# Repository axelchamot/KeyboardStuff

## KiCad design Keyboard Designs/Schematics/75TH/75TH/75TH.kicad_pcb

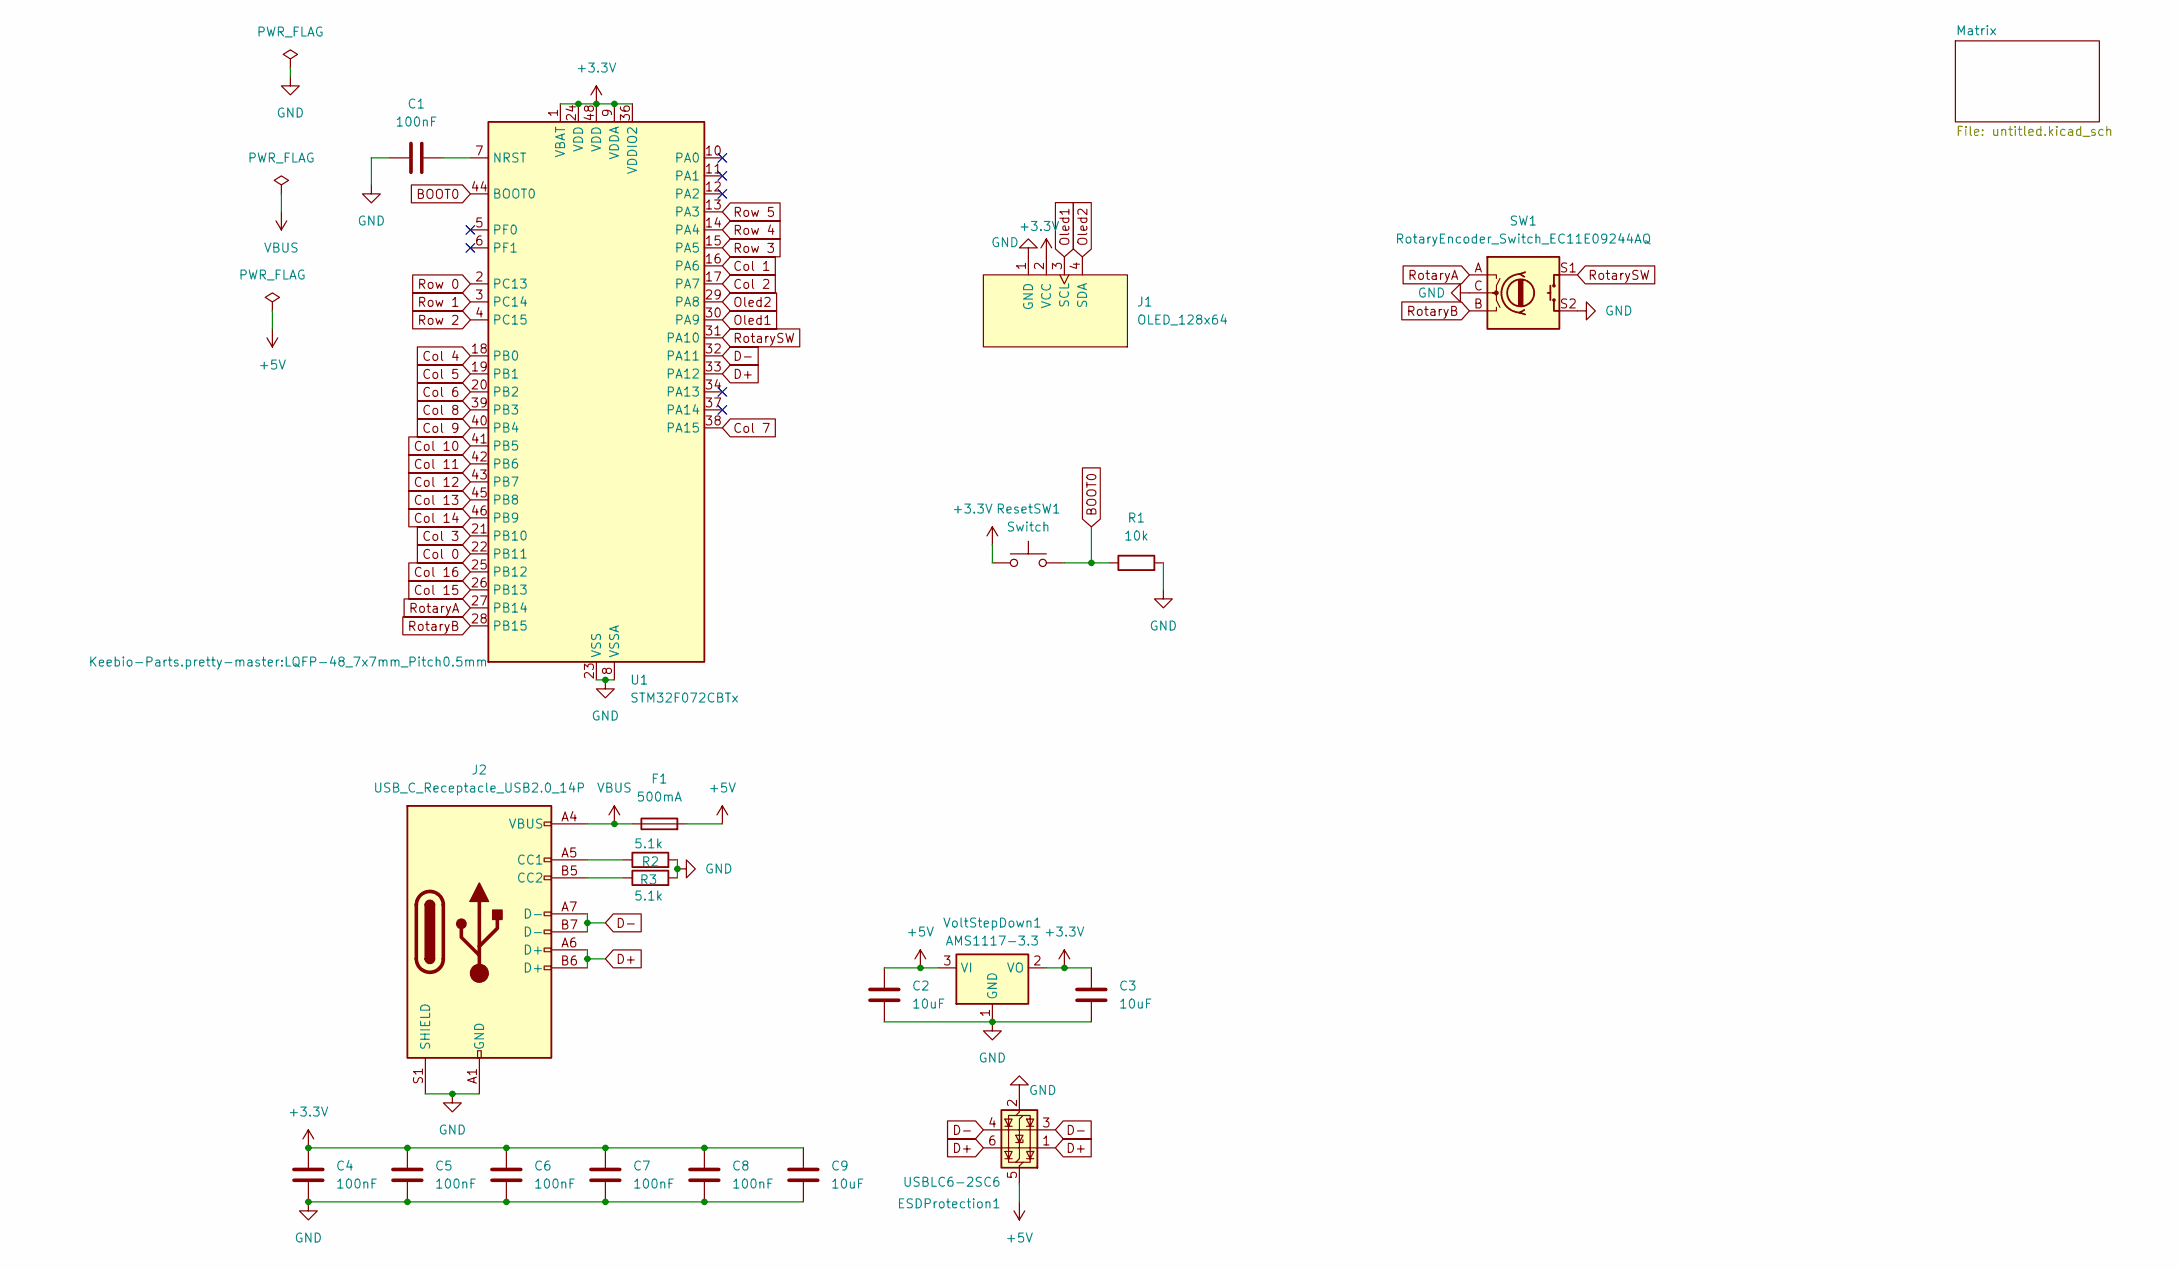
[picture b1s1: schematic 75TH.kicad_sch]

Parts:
C1, C4, C5, C6, C7, C8: 100nF; C_0805_2012Metric
C2, C3, C9: 10uF; C_0805_2012Metric
ESDProtection1: USBLC6-2SC6; SOT-23-6
F1: 500mA; Fuse_0603
J1: OLED_128x64
J2: USB_C_Receptacle_USB2.0_14P; USB_C_Receptacle_HRO_TYPE-C-31-M-12
R1: 10k; Resistor_0805
R2, R3: 5.1k; Resistor_0805
ResetSW1: Switch; SW_SPST_SKQG_WithStem
SW1: RotaryEncoder_Switch_EC11E09244AQ; RotaryEncoder_EC11
U1: STM32F072CBTx; LQFP-48_7x7mm_Pitch0.5mm
VoltStepDown1: AMS1117-3.3; SOT-223-3_TabPin2

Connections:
+3.3V: C3.1, C4.1, C5.1, C6.1, C7.1, C8.1, C9.1, J1.2 (VCC), ResetSW1.1, U1.1 (VBAT), U1.9 (VDDA), U1.24 (VDD), U1.36 (VDDIO2), U1.48 (VDD), VoltStepDown1.2 (VO)
+5V: C2.1, ESDProtection1.5 (VBUS), F1.2, VoltStepDown1.3 (VI)
BOOT0: R1.1, ResetSW1.2, U1.44 (BOOT0)
Col 0: U1.22 (PB11); also elsewhere on the board
Col 1: U1.16 (PA6); also elsewhere on the board
Col 2: U1.17 (PA7); also elsewhere on the board
Col 3: U1.21 (PB10); also elsewhere on the board
Col 4: U1.18 (PB0); also elsewhere on the board
Col 5: U1.19 (PB1); also elsewhere on the board
Col 6: U1.20 (PB2); also elsewhere on the board
Col 7: U1.38 (PA15); also elsewhere on the board
Col 8: U1.39 (PB3); also elsewhere on the board
Col 9: U1.40 (PB4); also elsewhere on the board
Col 10: U1.41 (PB5); also elsewhere on the board
Col 11: U1.42 (PB6); also elsewhere on the board
Col 12: U1.43 (PB7); also elsewhere on the board
Col 13: U1.45 (PB8); also elsewhere on the board
Col 14: U1.46 (PB9); also elsewhere on the board
Col 15: U1.26 (PB13); also elsewhere on the board
Col 16: U1.25 (PB12); also elsewhere on the board
D+: ESDProtection1.1 (I/O1), ESDProtection1.6 (I/O1), J2.A6 (D+), J2.B6 (D+), U1.33 (PA12)
D-: ESDProtection1.3 (I/O2), ESDProtection1.4 (I/O2), J2.A7 (D-), J2.B7 (D-), U1.32 (PA11)
GND: C1.1, C2.2, C3.2, C4.2, C5.2, C6.2, C7.2, C8.2, C9.2, ESDProtection1.2 (GND), J1.1 (GND), J2.A1 (GND), J2.A12 (GND), J2.B1 (GND), J2.B12 (GND), J2.S1 (SHIELD), R1.2, R2.2, R3.2, SW1.C, SW1.S2, U1.8 (VSSA), U1.23 (VSS), U1.35 (VSS), U1.47 (VSS), VoltStepDown1.1 (GND)
unnamed: J2.A5 (CC1), R2.1
unnamed: J2.B5 (CC2), R3.1
unnamed: C1.2, U1.7 (NRST)
Oled1: J1.3 (SCL), U1.30 (PA9)
Oled2: J1.4 (SDA), U1.29 (PA8)
RotaryA: SW1.A, U1.27 (PB14)
RotaryB: SW1.B, U1.28 (PB15)
RotarySW: SW1.S1, U1.31 (PA10)
Row 0: U1.2 (PC13); also elsewhere on the board
Row 1: U1.3 (PC14); also elsewhere on the board
Row 2: U1.4 (PC15); also elsewhere on the board
Row 3: U1.15 (PA5); also elsewhere on the board
Row 4: U1.14 (PA4); also elsewhere on the board
Row 5: U1.13 (PA3); also elsewhere on the board
VBUS: F1.1, J2.A4 (VBUS), J2.A9 (VBUS), J2.B4 (VBUS), J2.B9 (VBUS)

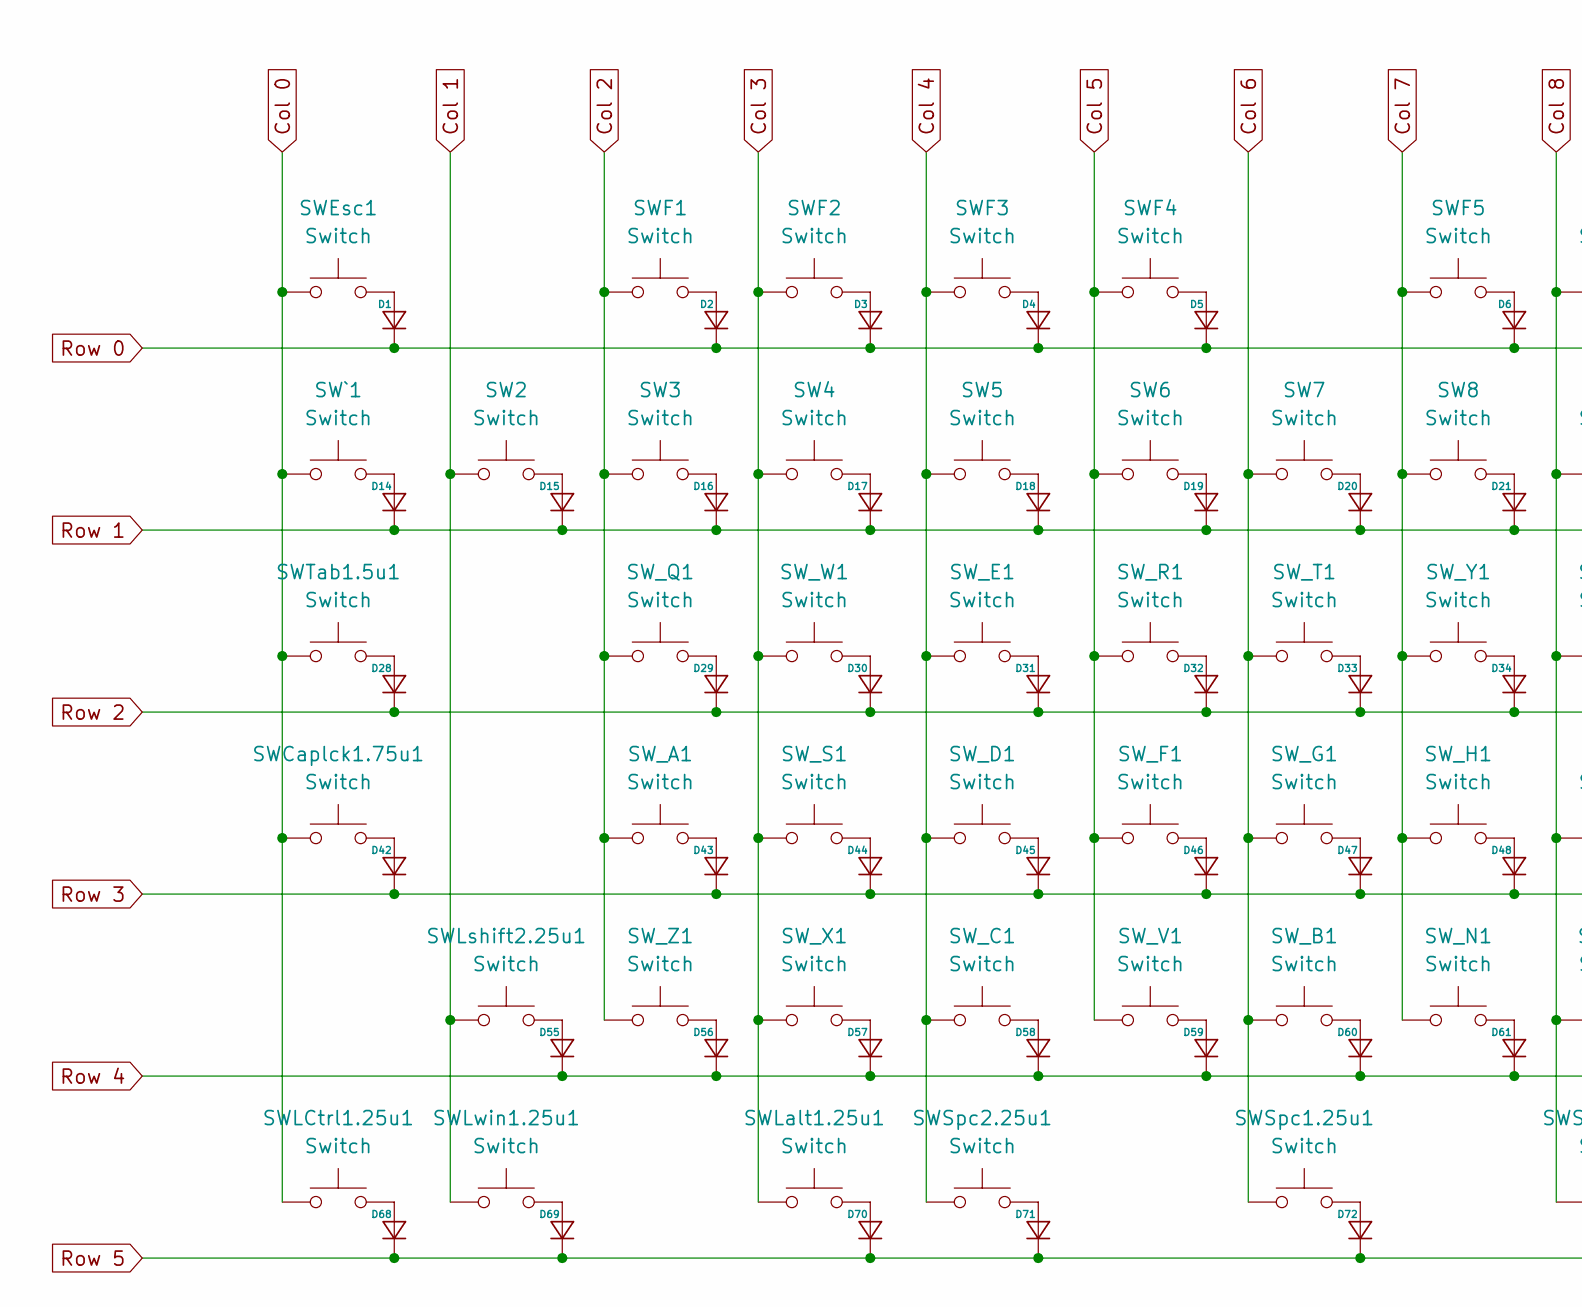
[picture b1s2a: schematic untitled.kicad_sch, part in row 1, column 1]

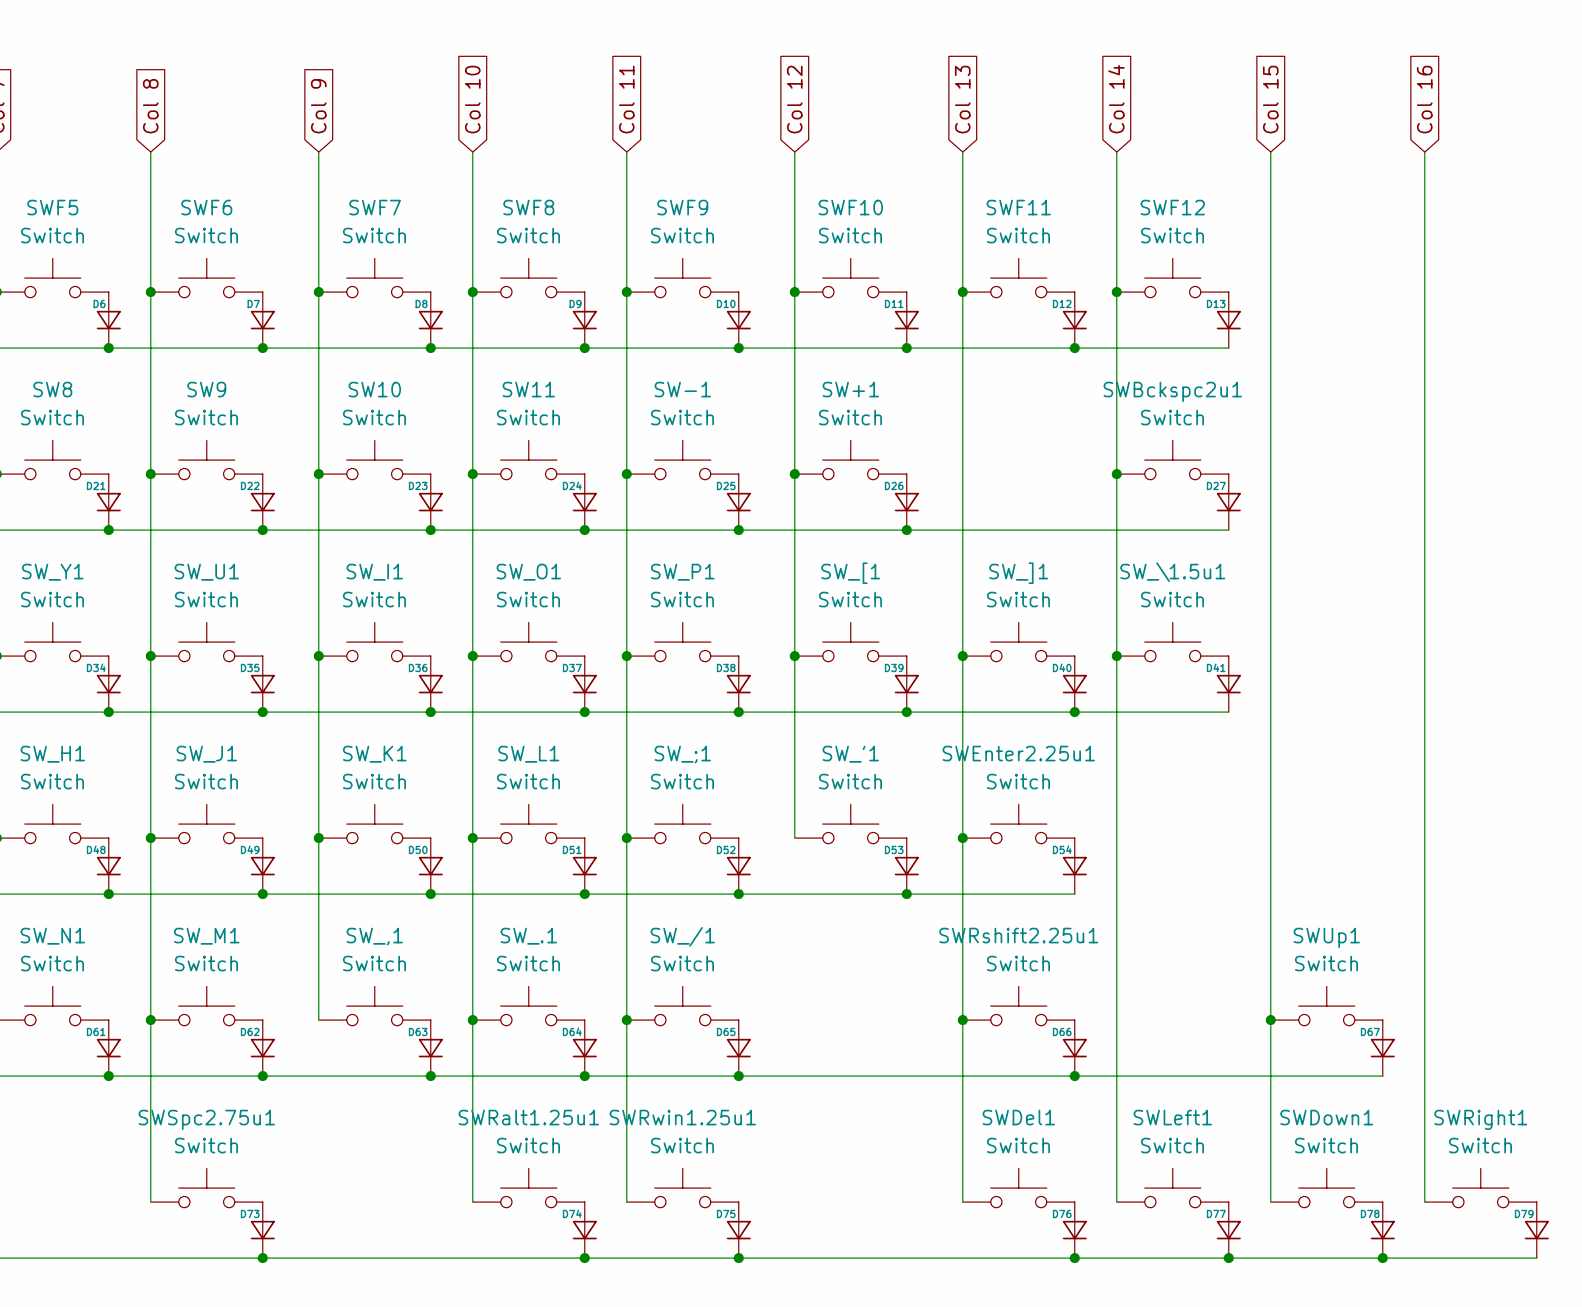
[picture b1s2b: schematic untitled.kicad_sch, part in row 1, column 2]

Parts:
D1, D2, D3, D4, D5, D6, D7, D8, D9, D10, D11, D12, D13, D14, D15, D16, D17, D18, D19, D20, D21, D22, D23, D24, D25, D26, D27, D28, D29, D30, D31, D32, D33, D34, D35, D36, D37, D38, D39, D40, D41, D42, D43, D44, D45, D46, D47, D48, D49, D50, D51, D52, D53, D54, D55, D56, D57, D58, D59, D60, D61, D62, D63, D64, D65, D66, D67, D68, D69, D70, D71, D72, D73, D74, D75, D76, D77, D78, D79: D_DO-35_SOD27_P7.62mm_Horizontal
SW2, SW3, SW4, SW5, SW6, SW7, SW8, SW9, SW10, SW11: Switch; SW_MX_1u
SW+1: Switch; SW_MX_1u
SW-1: Switch; SW_MX_1u
SWBckspc2u1: Switch; SW_MX_1u
SWCaplck1.75u1: Switch; SW_MX_1.75u
SWDel1: Switch; SW_MX_1u
SWDown1: Switch; SW_MX_1u
SWEnter2.25u1: Switch; SW_MX_1u
SWEsc1: Switch; SW_MX_1u
SWF1, SWF2, SWF3, SWF4, SWF5, SWF6, SWF7, SWF8, SWF9, SWF10, SWF11, SWF12: Switch; SW_MX_1u
SWLCtrl1.25u1: Switch; SW_MX_1.25u
SWLalt1.25u1: Switch; SW_MX_1.25u
SWLeft1: Switch; SW_MX_1u
SWLshift2.25u1: Switch; SW_MX_1u
SWLwin1.25u1: Switch; SW_MX_1.25u
SWRalt1.25u1: Switch; SW_MX_1.25u
SWRight1: Switch; SW_MX_1u
SWRshift2.25u1: Switch; SW_MX_1u
SWRwin1.25u1: Switch; SW_MX_1.25u
SWSpc1.25u1: Switch; SW_MX_1.25u
SWSpc2.25u1, SWSpc2.75u1: Switch; SW_MX_1u
SWTab1.5u1: Switch; SW_MX_1.5u
SWUp1: Switch; SW_MX_1u
SW_'1: Switch; SW_MX_1u
SW_,1: Switch; SW_MX_1u
SW_.1: Switch; SW_MX_1u
SW_/1: Switch; SW_MX_1u
SW_;1: Switch; SW_MX_1u
SW_A1: Switch; SW_MX_1u
SW_B1: Switch; SW_MX_1u
SW_C1: Switch; SW_MX_1u
SW_D1: Switch; SW_MX_1u
SW_E1: Switch; SW_MX_1u
SW_F1: Switch; SW_MX_1u
SW_G1: Switch; SW_MX_1u
SW_H1: Switch; SW_MX_1u
SW_I1: Switch; SW_MX_1u
SW_J1: Switch; SW_MX_1u
SW_K1: Switch; SW_MX_1u
SW_L1: Switch; SW_MX_1u
SW_M1: Switch; SW_MX_1u
SW_N1: Switch; SW_MX_1u
SW_O1: Switch; SW_MX_1u
SW_P1: Switch; SW_MX_1u
SW_Q1: Switch; SW_MX_1u
SW_R1: Switch; SW_MX_1u
SW_S1: Switch; SW_MX_1u
SW_T1: Switch; SW_MX_1u
SW_U1: Switch; SW_MX_1u
SW_V1: Switch; SW_MX_1u
SW_W1: Switch; SW_MX_1u
SW_X1: Switch; SW_MX_1u
SW_Y1: Switch; SW_MX_1u
SW_Z1: Switch; SW_MX_1u
SW_[1: Switch; SW_MX_1u
SW_\1.5u1: Switch; SW_MX_1.5u
SW_]1: Switch; SW_MX_1u
SW`1: Switch; SW_MX_1u

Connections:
Col 0: SWCaplck1.75u1.1, SWEsc1.1, SWLCtrl1.25u1.1, SWTab1.5u1.1, SW`1.1; also elsewhere on the board
Col 1: SW2.1, SWLshift2.25u1.1, SWLwin1.25u1.1; also elsewhere on the board
Col 2: SW3.1, SWF1.1, SW_A1.1, SW_Q1.1, SW_Z1.1; also elsewhere on the board
Col 3: SW4.1, SWF2.1, SWLalt1.25u1.1, SW_S1.1, SW_W1.1, SW_X1.1; also elsewhere on the board
Col 4: SW5.1, SWF3.1, SWSpc2.25u1.1, SW_C1.1, SW_D1.1, SW_E1.1; also elsewhere on the board
Col 5: SW6.1, SWF4.1, SW_F1.1, SW_R1.1, SW_V1.1; also elsewhere on the board
Col 6: SW7.1, SWSpc1.25u1.1, SW_B1.1, SW_G1.1, SW_T1.1; also elsewhere on the board
Col 7: SW8.1, SWF5.1, SW_H1.1, SW_N1.1, SW_Y1.1; also elsewhere on the board
Col 8: SW9.1, SWF6.1, SWSpc2.75u1.1, SW_J1.1, SW_M1.1, SW_U1.1; also elsewhere on the board
Col 9: SW10.1, SWF7.1, SW_,1.1, SW_I1.1, SW_K1.1; also elsewhere on the board
Col 10: SW11.1, SWF8.1, SWRalt1.25u1.1, SW_.1.1, SW_L1.1, SW_O1.1; also elsewhere on the board
Col 11: SW-1.1, SWF9.1, SWRwin1.25u1.1, SW_/1.1, SW_;1.1, SW_P1.1; also elsewhere on the board
Col 12: SW+1.1, SWF10.1, SW_'1.1, SW_[1.1; also elsewhere on the board
Col 13: SWDel1.1, SWEnter2.25u1.1, SWF11.1, SWRshift2.25u1.1, SW_]1.1; also elsewhere on the board
Col 14: SWBckspc2u1.1, SWF12.1, SWLeft1.1, SW_\1.5u1.1; also elsewhere on the board
Col 15: SWDown1.1, SWUp1.1; also elsewhere on the board
Col 16: SWRight1.1; also elsewhere on the board
unnamed: D1.2 (A), SWEsc1.2
unnamed: D2.2 (A), SWF1.2
unnamed: D3.2 (A), SWF2.2
unnamed: D4.2 (A), SWF3.2
unnamed: D5.2 (A), SWF4.2
unnamed: D6.2 (A), SWF5.2
unnamed: D7.2 (A), SWF6.2
unnamed: D8.2 (A), SWF7.2
unnamed: D9.2 (A), SWF8.2
unnamed: D10.2 (A), SWF9.2
unnamed: D11.2 (A), SWF10.2
unnamed: D12.2 (A), SWF11.2
unnamed: D13.2 (A), SWF12.2
unnamed: D14.2 (A), SW`1.2
unnamed: D15.2 (A), SW2.2
unnamed: D16.2 (A), SW3.2
unnamed: D17.2 (A), SW4.2
unnamed: D18.2 (A), SW5.2
unnamed: D19.2 (A), SW6.2
unnamed: D20.2 (A), SW7.2
unnamed: D21.2 (A), SW8.2
unnamed: D22.2 (A), SW9.2
unnamed: D23.2 (A), SW10.2
unnamed: D24.2 (A), SW11.2
unnamed: D25.2 (A), SW-1.2
unnamed: D26.2 (A), SW+1.2
unnamed: D27.2 (A), SWBckspc2u1.2
unnamed: D28.2 (A), SWTab1.5u1.2
unnamed: D29.2 (A), SW_Q1.2
unnamed: D30.2 (A), SW_W1.2
unnamed: D31.2 (A), SW_E1.2
unnamed: D32.2 (A), SW_R1.2
unnamed: D33.2 (A), SW_T1.2
unnamed: D34.2 (A), SW_Y1.2
unnamed: D35.2 (A), SW_U1.2
unnamed: D36.2 (A), SW_I1.2
unnamed: D37.2 (A), SW_O1.2
unnamed: D38.2 (A), SW_P1.2
unnamed: D39.2 (A), SW_[1.2
unnamed: D40.2 (A), SW_]1.2
unnamed: D41.2 (A), SW_\1.5u1.2
unnamed: D42.2 (A), SWCaplck1.75u1.2
unnamed: D43.2 (A), SW_A1.2
unnamed: D44.2 (A), SW_S1.2
unnamed: D45.2 (A), SW_D1.2
unnamed: D46.2 (A), SW_F1.2
unnamed: D47.2 (A), SW_G1.2
unnamed: D48.2 (A), SW_H1.2
unnamed: D49.2 (A), SW_J1.2
unnamed: D50.2 (A), SW_K1.2
unnamed: D51.2 (A), SW_L1.2
unnamed: D52.2 (A), SW_;1.2
unnamed: D53.2 (A), SW_'1.2
unnamed: D54.2 (A), SWEnter2.25u1.2
unnamed: D55.2 (A), SWLshift2.25u1.2
unnamed: D56.2 (A), SW_Z1.2
unnamed: D57.2 (A), SW_X1.2
unnamed: D58.2 (A), SW_C1.2
unnamed: D59.2 (A), SW_V1.2
unnamed: D60.2 (A), SW_B1.2
unnamed: D61.2 (A), SW_N1.2
unnamed: D62.2 (A), SW_M1.2
unnamed: D63.2 (A), SW_,1.2
unnamed: D64.2 (A), SW_.1.2
unnamed: D65.2 (A), SW_/1.2
unnamed: D66.2 (A), SWRshift2.25u1.2
unnamed: D67.2 (A), SWUp1.2
unnamed: D68.2 (A), SWLCtrl1.25u1.2
unnamed: D69.2 (A), SWLwin1.25u1.2
unnamed: D70.2 (A), SWLalt1.25u1.2
unnamed: D71.2 (A), SWSpc2.25u1.2
unnamed: D72.2 (A), SWSpc1.25u1.2
unnamed: D73.2 (A), SWSpc2.75u1.2
unnamed: D74.2 (A), SWRalt1.25u1.2
unnamed: D75.2 (A), SWRwin1.25u1.2
unnamed: D76.2 (A), SWDel1.2
unnamed: D77.2 (A), SWLeft1.2
unnamed: D78.2 (A), SWDown1.2
unnamed: D79.2 (A), SWRight1.2
Row 0: D1.1 (K), D2.1 (K), D3.1 (K), D4.1 (K), D5.1 (K), D6.1 (K), D7.1 (K), D8.1 (K), D9.1 (K), D10.1 (K), D11.1 (K), D12.1 (K), D13.1 (K); also elsewhere on the board
Row 1: D14.1 (K), D15.1 (K), D16.1 (K), D17.1 (K), D18.1 (K), D19.1 (K), D20.1 (K), D21.1 (K), D22.1 (K), D23.1 (K), D24.1 (K), D25.1 (K), D26.1 (K), D27.1 (K); also elsewhere on the board
Row 2: D28.1 (K), D29.1 (K), D30.1 (K), D31.1 (K), D32.1 (K), D33.1 (K), D34.1 (K), D35.1 (K), D36.1 (K), D37.1 (K), D38.1 (K), D39.1 (K), D40.1 (K), D41.1 (K); also elsewhere on the board
Row 3: D42.1 (K), D43.1 (K), D44.1 (K), D45.1 (K), D46.1 (K), D47.1 (K), D48.1 (K), D49.1 (K), D50.1 (K), D51.1 (K), D52.1 (K), D53.1 (K), D54.1 (K); also elsewhere on the board
Row 4: D55.1 (K), D56.1 (K), D57.1 (K), D58.1 (K), D59.1 (K), D60.1 (K), D61.1 (K), D62.1 (K), D63.1 (K), D64.1 (K), D65.1 (K), D66.1 (K), D67.1 (K); also elsewhere on the board
Row 5: D68.1 (K), D69.1 (K), D70.1 (K), D71.1 (K), D72.1 (K), D73.1 (K), D74.1 (K), D75.1 (K), D76.1 (K), D77.1 (K), D78.1 (K), D79.1 (K); also elsewhere on the board

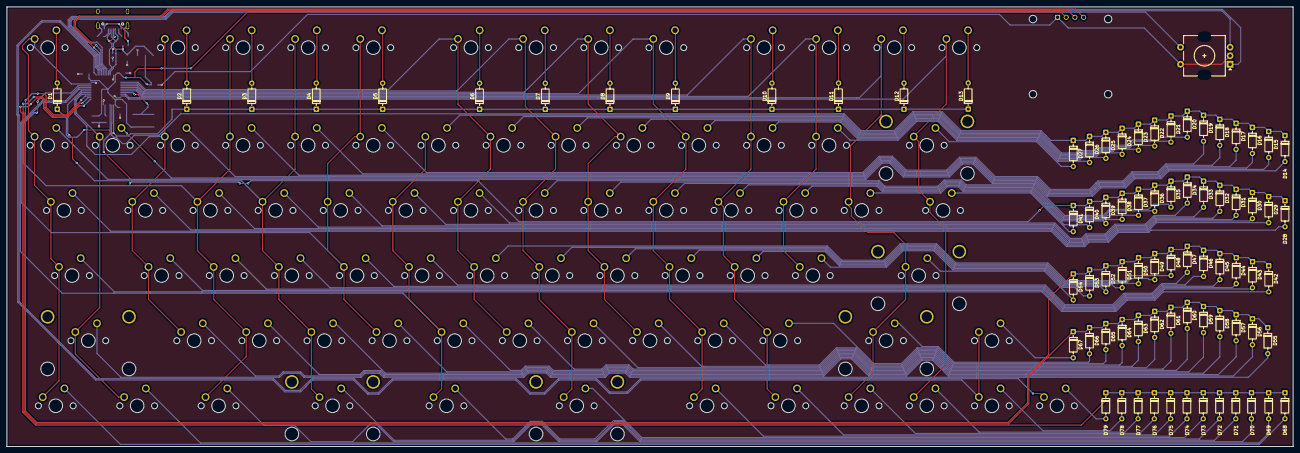
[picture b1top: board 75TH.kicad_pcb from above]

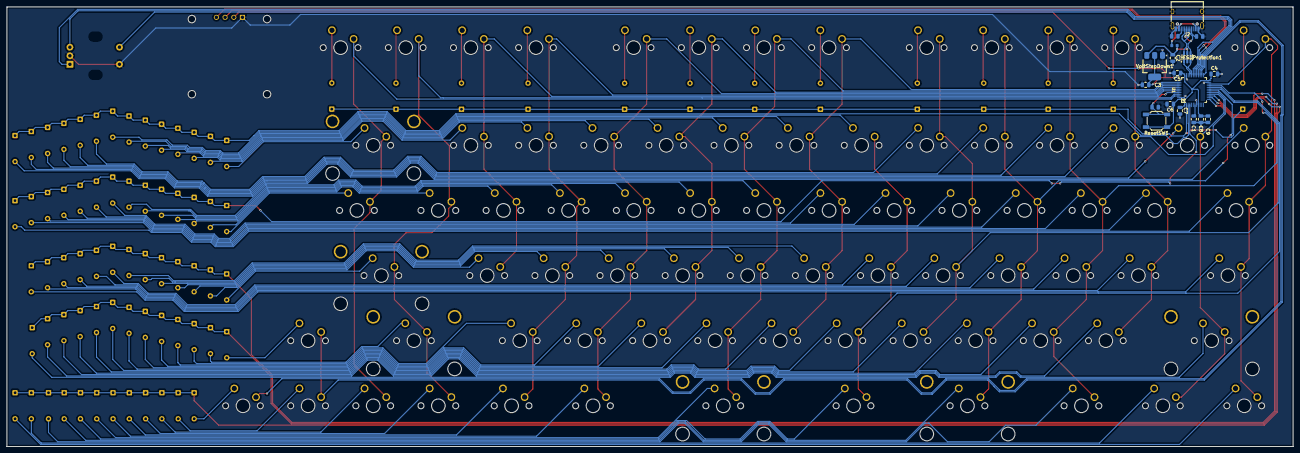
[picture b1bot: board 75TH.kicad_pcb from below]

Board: 2 copper layers, 376.2 x 128.6 mm, 178 parts (18 on the bottom side), 117 nets.

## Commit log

2025-09-02 added footprints
2025-09-02 Added more component footprints
2025-12-05 Matrix Made
2025-12-06 Started pcb layout
2025-12-07 wired usbc and partial MCU
2025-12-07 Added more traces
2025-12-10 Changed diodes and redoing matrix
2025-12-10 Finished traces
